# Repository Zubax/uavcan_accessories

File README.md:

# UAVCAN_ACCESSORIES
Some accessories to make life of UAVCAN hobbiyists easier
At the moment three devices exist here:

* DCP2PLS
* DB9_2_JST_GH
* UAVCAN_HUB

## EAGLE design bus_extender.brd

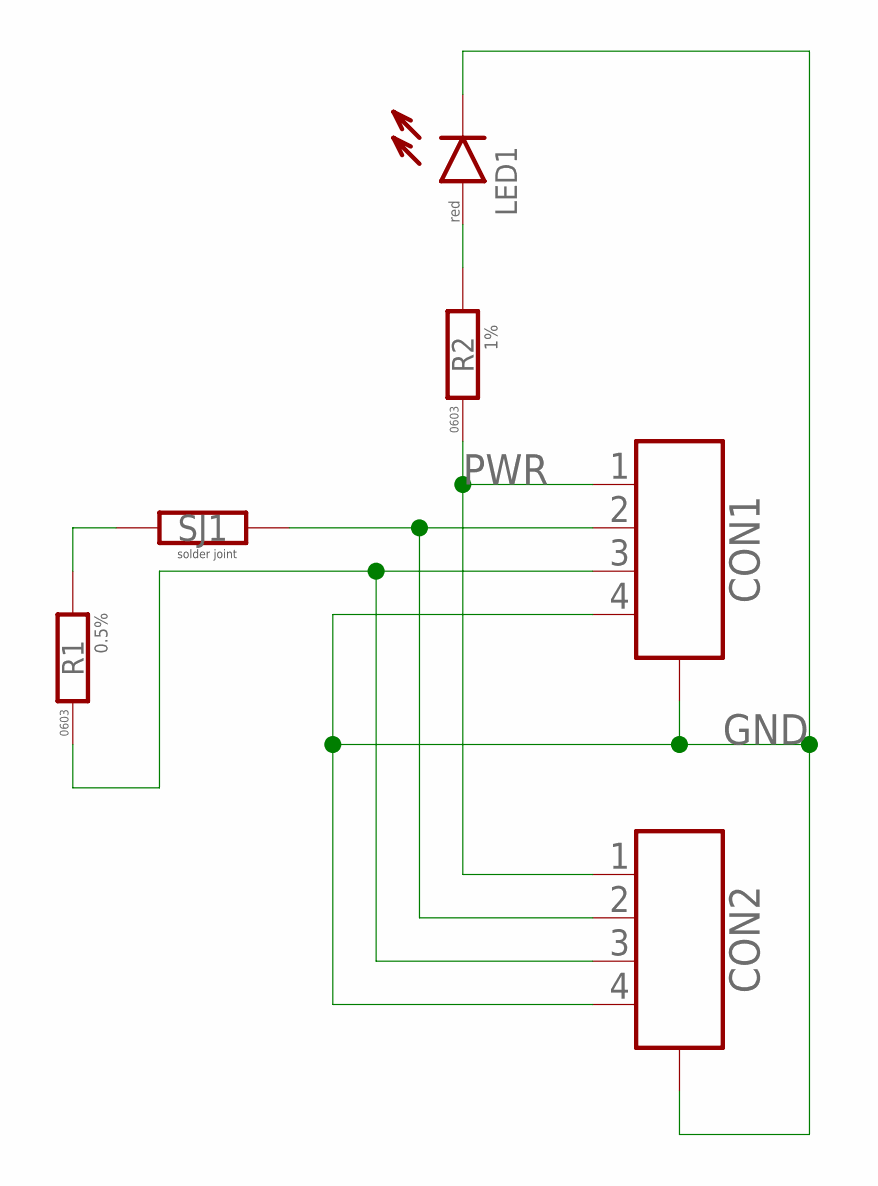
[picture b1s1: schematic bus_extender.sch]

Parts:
CON1, CON2: CON-4P-TABS-JST_GH-RA; JST_GH-4P-RA
LED1: LED-0603; LED0603; DIGIKEY# 511-1587-1-ND
R1: R-1%-0603; R0603; TOLERANCE 0.5%; DIGIKEY# 311-121DCT-ND
R2: R-1%-0603; R0603; DIGIKEY# RHM200ADCT-ND
SJ1: SOLDER_JOINT; RES_0

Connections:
GND: CON1.4, CON1.M$0 (GND), CON1.M$1 (GND), CON2.4, CON2.M$0 (GND), CON2.M$1 (GND), LED1.C
unnamed: LED1.A, R2.2
unnamed: CON1.2, CON2.2, SJ1.2
unnamed: CON1.3, CON2.3, R1.1
unnamed: R1.2, SJ1.1
PWR: CON1.1, CON2.1, R2.1

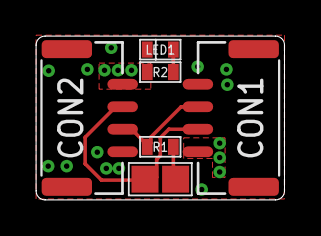
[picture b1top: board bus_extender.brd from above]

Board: 2 copper layers, 13.8 x 9.1 mm, 6 parts (0 on the bottom side), 6 nets.

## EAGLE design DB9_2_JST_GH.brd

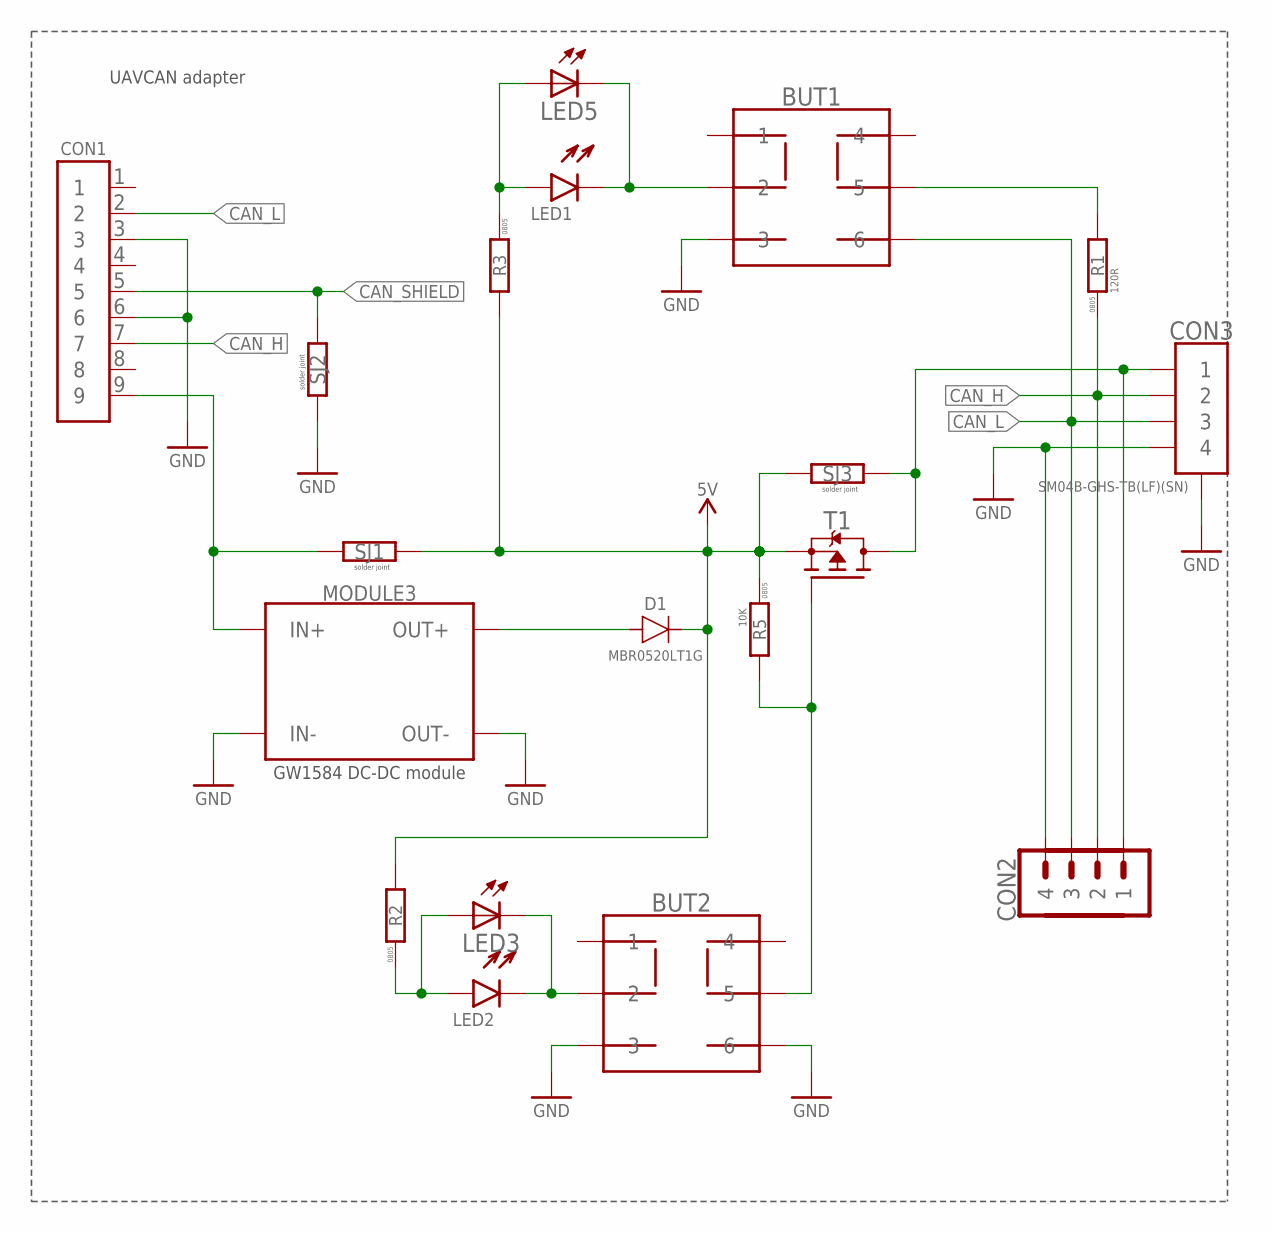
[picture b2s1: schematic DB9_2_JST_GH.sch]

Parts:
BUT1, BUT2: BUTTON; PBM-0112
CON1: DB9; D_SUB9
CON2: PINHEAD_1X04-2.54; 1X04-PTH-2.54
CON3: CON-4P-JST_GH; JST_GH-4P
D1: MBR0520L-SOD123; SOD123
LED1, LED2: LED-0805; LED0805
LED3, LED5: LED-3MM
MODULE3: GW1584
R1: 120R; R0805
R2, R3: R-0805; R0805
R5: 10K; R0805
SJ1, SJ2, SJ3: SOLDER_JOINT_2P; SJ_2P
T1: FDN302P-SOT23; SOT23B-3

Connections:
CAN_H: CON1.7, CON2.2, CON3.2, R1.1
CAN_L: BUT1.6, CON1.2, CON2.3, CON3.3
CAN_PWR: CON1.9, MODULE3.IN+@1 (IN+), MODULE3.IN+@2 (IN+), SJ1.1
CAN_SHIELD: CON1.5, SJ2.1
CAN_VDD_EN: BUT2.5, R5.2, T1.G
GND: BUT1.3, BUT2.3, BUT2.6, CON1.3, CON1.6, CON2.4, CON3.4, CON3.M$0 (GND), CON3.M$1 (GND), MODULE3.IN-@1 (IN-), MODULE3.IN-@2 (IN-), MODULE3.OUT-@1 (OUT-), MODULE3.OUT-@2 (OUT-), SJ2.2
unnamed: BUT2.2, LED2.C, LED3.K (C)
unnamed: BUT1.5, R1.2
unnamed: BUT1.2, LED1.C, LED5.K (C)
unnamed: LED1.A, LED5.A, R3.1
unnamed: D1.A, MODULE3.OUT+@1 (OUT+), MODULE3.OUT+@2 (OUT+)
unnamed: CON2.1, CON3.1, SJ3.2, T1.D
unnamed: LED2.A, LED3.A, R2.1
VDD_5V: D1.C, R2.2, R3.2, R5.1, SJ1.2, SJ3.1, T1.S

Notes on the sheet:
UAVCAN adapter

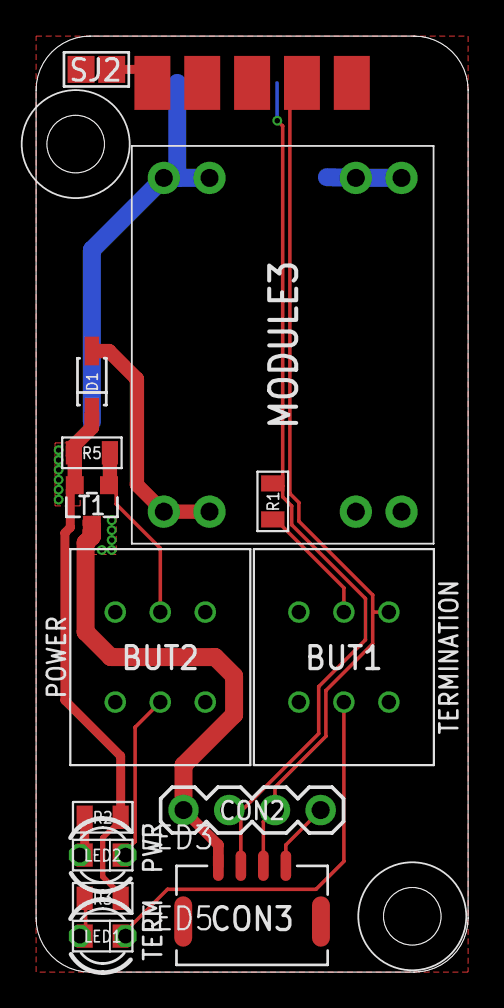
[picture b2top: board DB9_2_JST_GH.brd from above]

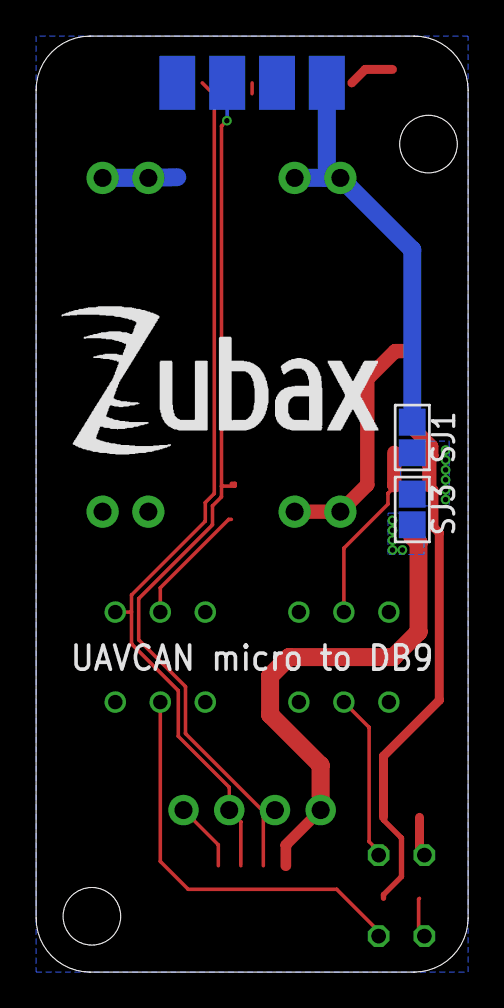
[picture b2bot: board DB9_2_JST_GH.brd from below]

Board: 2 copper layers, 24.0 x 52.0 mm, 20 parts (3 on the bottom side), 14 nets.

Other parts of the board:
U$13: ZUBAX_LOGO_18X8

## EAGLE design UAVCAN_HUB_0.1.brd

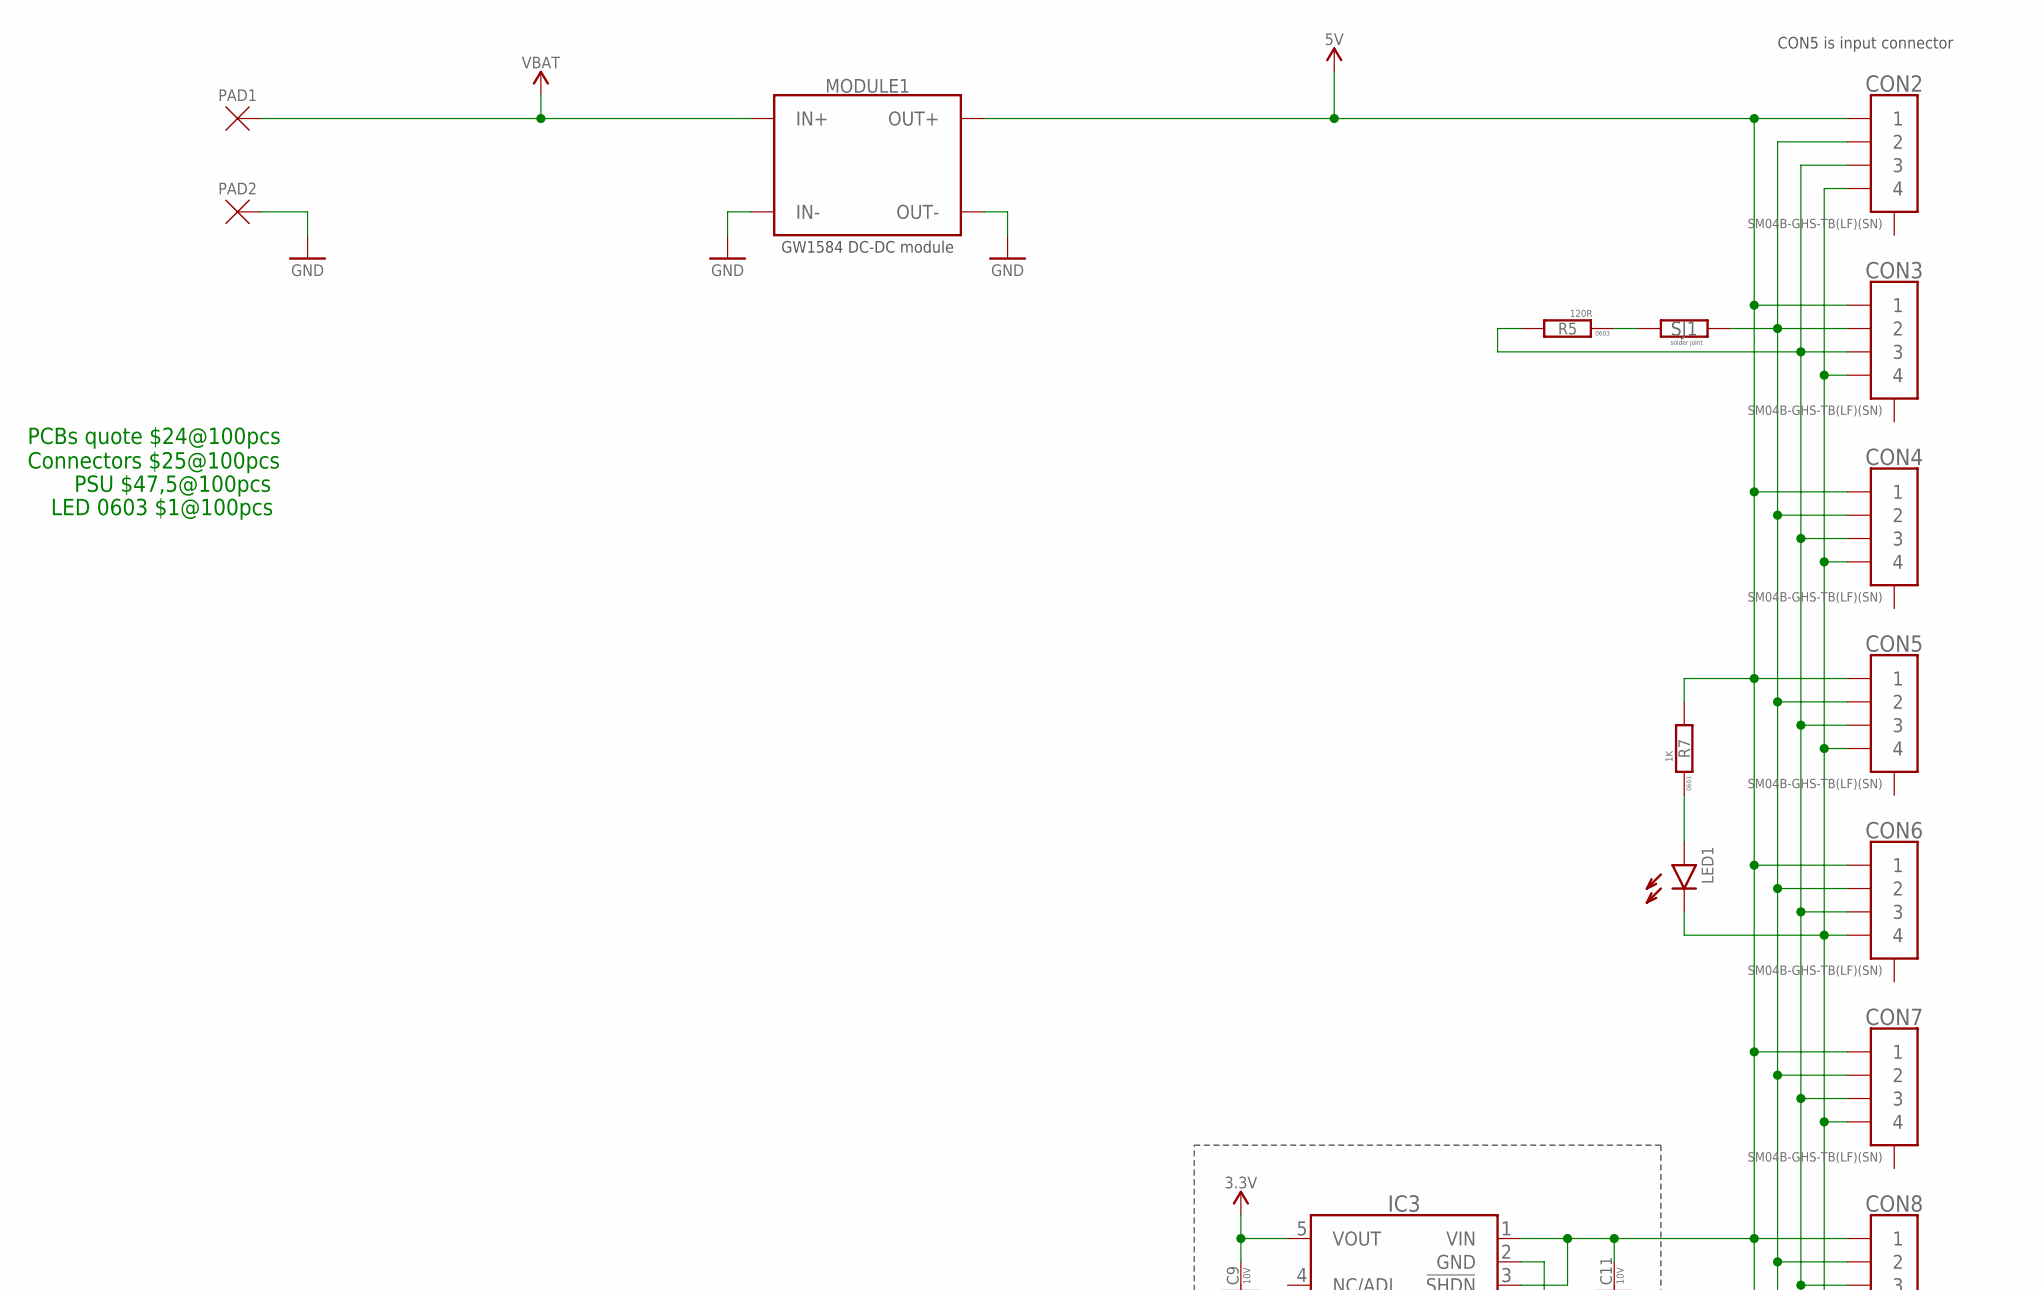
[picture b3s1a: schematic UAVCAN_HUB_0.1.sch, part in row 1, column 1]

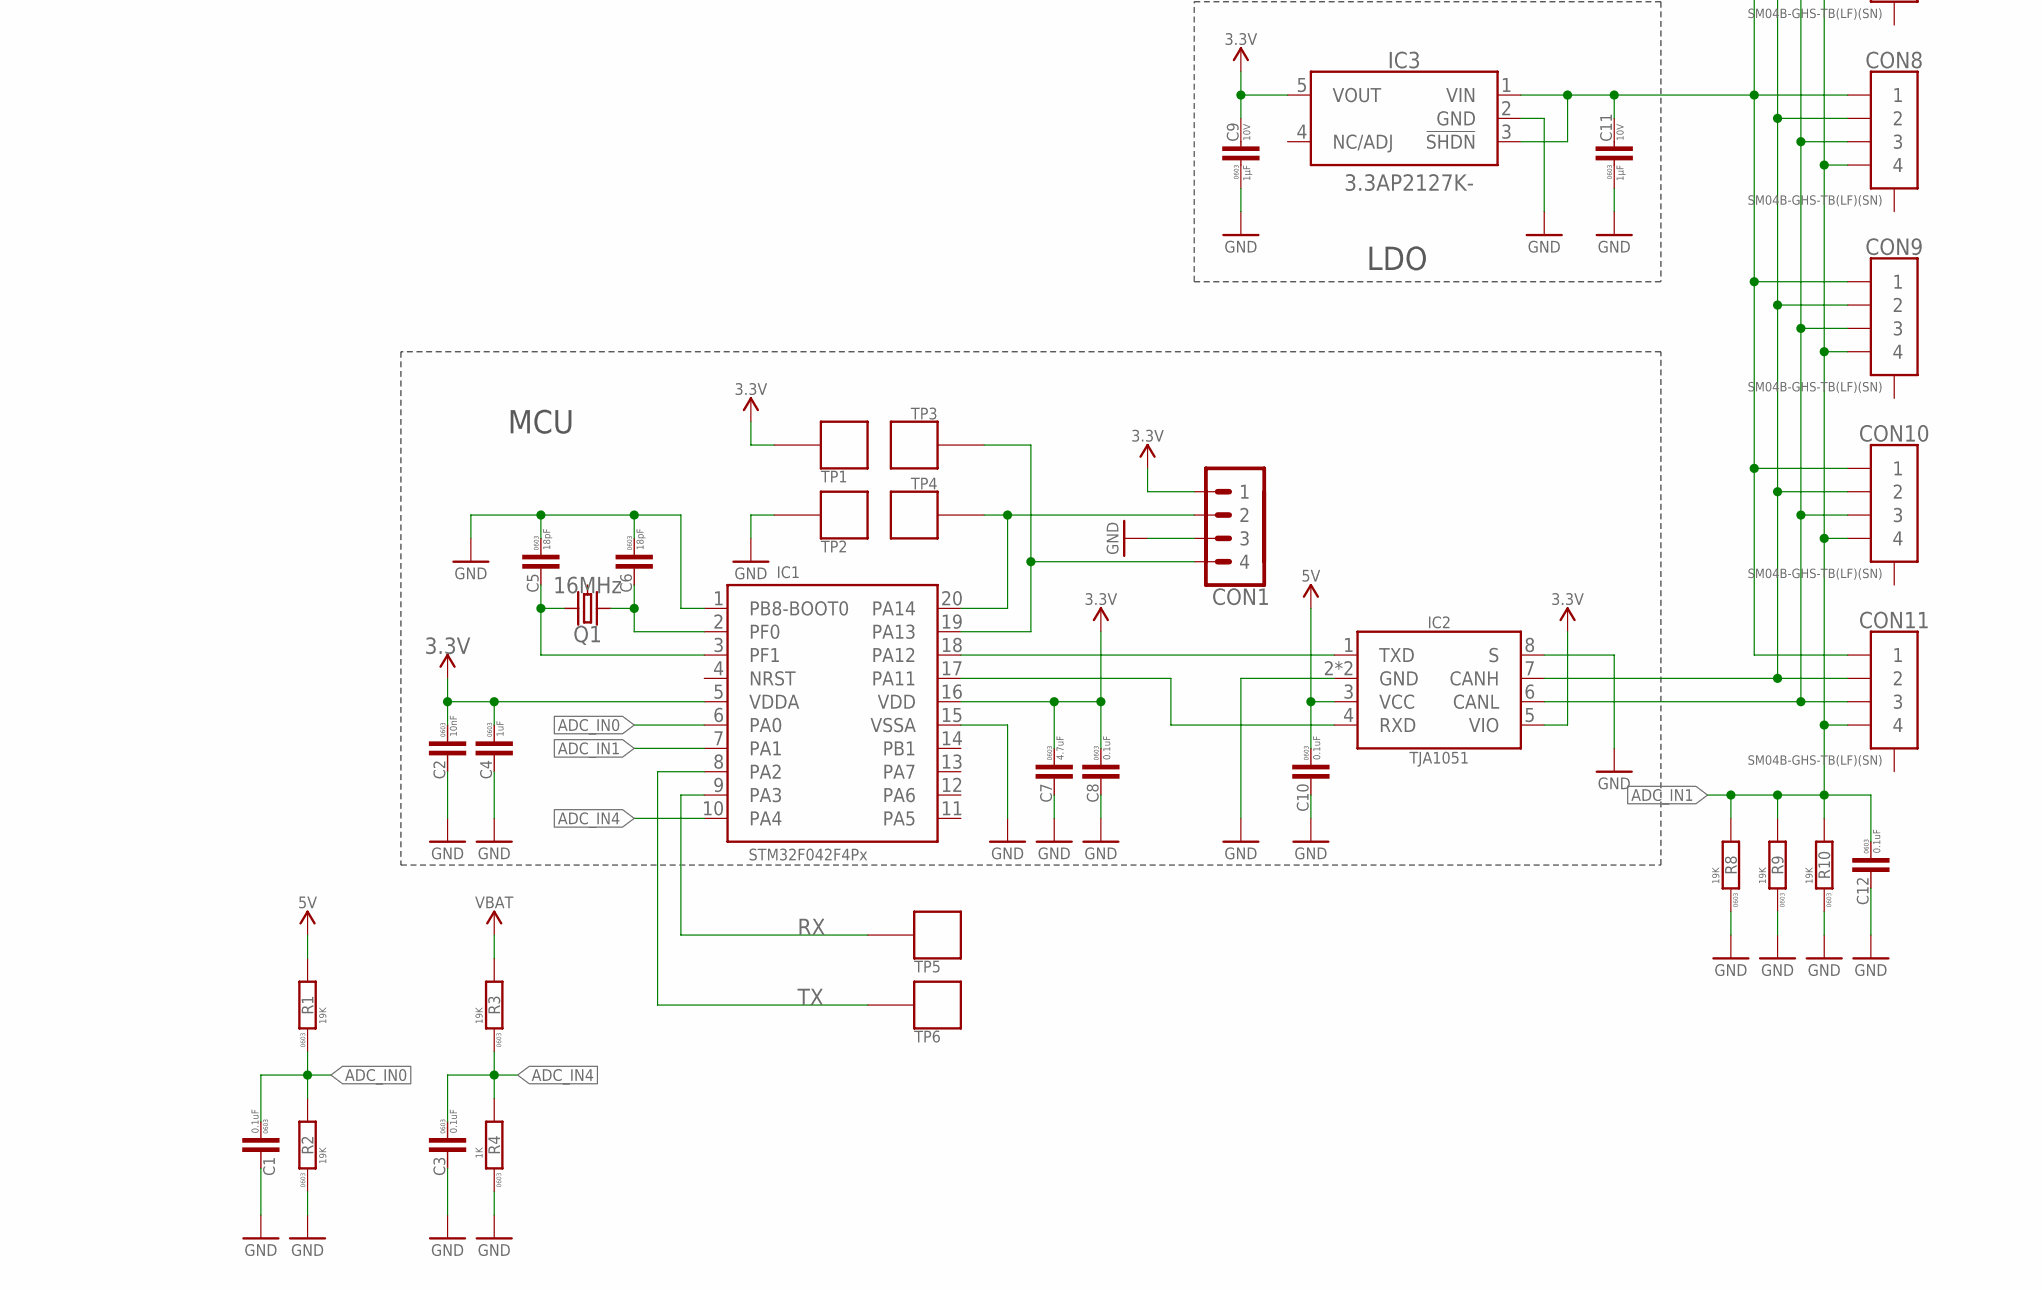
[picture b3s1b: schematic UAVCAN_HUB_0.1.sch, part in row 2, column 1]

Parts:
C1, C3, C8, C10, C12: 0.1uF; C0603
C2: 10nF; C0603
C4: 1uF; C0603
C5, C6: 18pF; C0603
C7: 4.7uF; C0603
C9, C11: 1µF; C0603
CON1: PINHEAD_1X04-2.54; 1X04-PTH-2.54
CON2, CON3, CON4, CON5, CON6, CON7, CON8, CON9, CON10, CON11: CON-4P-JST_GH; JST_GH-4P
IC1: STM32F042F4PX; TSSOP20
IC2: TJA1051; SOT782-1
IC3: 3.3; SOT23-5L
LED1: LED-0603; LED0603
MODULE1: GW1584
PAD1, PAD2: PAD-4X2; 4X2
Q1: 16MHz; OSCILLATOR-3.2X2.5
R1, R2, R3, R8, R9, R10: 19K; R0603
R4, R7: 1K; R0603
R5: 120R; R0603
SJ1: SOLDER_JOINT_2P; SJ_2P
TP1, TP2, TP3, TP4, TP5, TP6: PAD.05; PAD.05X.05; PARTNO *

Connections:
ADC_IN0: C1.1, IC1.6 (PA0), R1.1, R2.2
ADC_IN1: C12.1, CON2.4, CON3.4, CON4.4, CON5.4, CON6.4, CON7.4, CON8.4, CON9.4, CON10.4, CON11.4, IC1.7 (PA1), LED1.C, R8.2, R9.2, R10.2
ADC_IN4: C3.1, IC1.10 (PA4), R3.1, R4.2
CAN_RX: IC1.17 (PA11), IC2.4 (RXD)
CAN_TX: IC1.18 (PA12), IC2.1 (TXD)
GND: C1.2, C2.2, C3.2, C4.2, C5.1, C6.1, C7.2, C8.2, C9.P$1 (1), C10.2, C11.P$1 (1), C12.2, CON1.3, IC1.1 (PB8-BOOT0), IC1.15 (VSSA), IC2.2 (GND), IC2.8 (S), IC2.PAD (GND), IC3.2 (GND), MODULE1.IN-@1 (IN-), MODULE1.IN-@2 (IN-), MODULE1.OUT-@1 (OUT-), MODULE1.OUT-@2 (OUT-), PAD2.P$1, R2.1, R4.1, R8.1, R9.1, R10.1, TP2.P$1
unnamed: CON2.3, CON3.3, CON4.3, CON5.3, CON6.3, CON7.3, CON8.3, CON9.3, CON10.3, CON11.3, IC2.6 (CANL), R5.2
unnamed: C6.2, IC1.2 (PF0), Q1.1
unnamed: C5.2, IC1.3 (PF1), Q1.3 (2)
unnamed: CON1.4, IC1.19 (PA13), TP3.P$1
unnamed: LED1.A, R7.1
unnamed: R5.1, SJ1.1
unnamed: CON1.2, IC1.20 (PA14), TP4.P$1
unnamed: CON2.2, CON3.2, CON4.2, CON5.2, CON6.2, CON7.2, CON8.2, CON9.2, CON10.2, CON11.2, IC2.7 (CANH), SJ1.2
RX: IC1.9 (PA3), TP5.P$1
TX: IC1.8 (PA2), TP6.P$1
VBAT: MODULE1.IN+@1 (IN+), MODULE1.IN+@2 (IN+), PAD1.P$1, R3.2
VDD_3V3: C2.1, C4.1, C7.1, C8.1, C9.P$2 (2), CON1.1, IC1.5 (VDDA), IC1.16 (VDD), IC2.5 (VIO), IC3.5 (VOUT), TP1.P$1
VDD_5V: C10.1, C11.P$2 (2), CON2.1, CON3.1, CON4.1, CON5.1, CON6.1, CON7.1, CON8.1, CON9.1, CON10.1, CON11.1, IC2.3 (VCC), IC3.1 (VIN), IC3.3 (!SHDN), MODULE1.OUT+@1 (OUT+), MODULE1.OUT+@2 (OUT+), R1.2, R7.2

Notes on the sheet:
CON5 is input connector
PCBs quote $24@100pcs Connectors $25@100pcs
PSU $47,5@100pcs
LED 0603 $1@100pcs
MCU
LDO

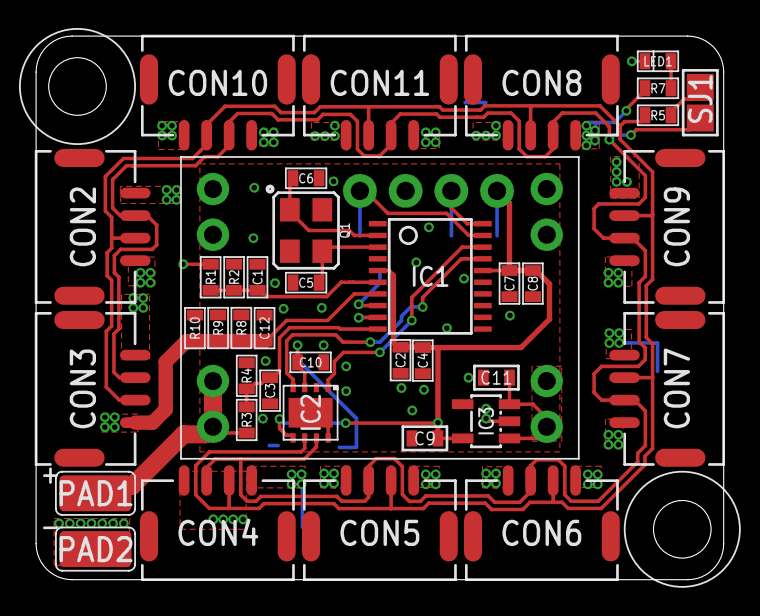
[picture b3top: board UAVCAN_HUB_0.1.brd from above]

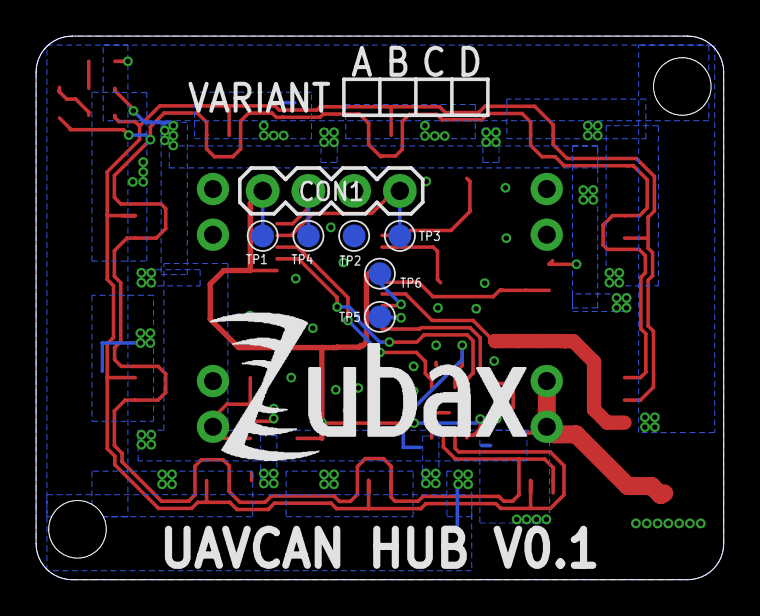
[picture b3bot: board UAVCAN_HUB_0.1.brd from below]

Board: 2 copper layers, 38.2 x 30.2 mm, 48 parts (8 on the bottom side), 19 nets.

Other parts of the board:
U$13: ZUBAX_LOGO_18X8

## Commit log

2018-03-22 initial import
2020-06-22 bus extender import
2023-11-22 added part numbers
    R1, R2, and LED1
2023-11-22 Added part numbers for R1, R2, and LED1 (#1)
